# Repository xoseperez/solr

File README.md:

# Solr

The **Solr digital wrist watch** is a clock that won’t work without a battery but it will neither work without sun. Even more: the vintage display is really cool but it’s hard to read outdoors. A complete nonsense.

Check my **blog post** to know more about it: [Solr: digital wrist watch](http://tinkerman.cat/solr-digital-wrist-watch/)

## Hardware

I strongly recommend to find some provider that can assembly at least the HMC5883L, it's a really hard to chip to solder manually. The rest of the components are quite easy to do.

### BOM as exported from Eagle

|Part|Value|Package|Buy|
|---|---|---|---|
|BATT||CR2032-SMD|.|
|C1|100nf|C0805|.|
|C2|4.7uf|AVX-A|.|
|C3|220nf|C0805|.|
|C4|100nf|C0805|.|
|CHECK||BTN_CK_KSS|[Aliexpress](http://s.click.aliexpress.com/e/MrBaM7q)|
|IC1|ATMEGA328P-AU-TQFP32|TQFP32-0.8-7X7MM|[Aliexpress](http://s.click.aliexpress.com/e/Y3FMzZV)|
|IC2|HMC5883L|PLCC16-0.5-3X3MM|[Aliexpress](http://s.click.aliexpress.com/e/bIAm2zB) / [Ebay](https://rover.ebay.com/rover/1/711-53200-19255-0/1?icep_id=114&ipn=icep&toolid=20004&campid=5338044841&mpre=http%3A%2F%2Fwww.ebay.com%2Fitm%2F1x-NEW-HONEYWELL-HMC5883L-HMC-5883L-LCC16-LCC-16-IC-CHIPS-%2F321121197770)|
|LED1|HP QDSP-6064||[Ebay](https://rover.ebay.com/rover/1/1185-53479-19255-0/1?icep_id=114&ipn=icep&toolid=20004&campid=5338044841&mpre=http%3A%2F%2Fwww.ebay.es%2Fitm%2FRetro-4-digit-BUBBLE-VINTAGE-rare-red-LED-Display-QDSP6064-NOS-%2F152160249337)|
|R1|82R|R0805|.|
|R2|82R|R0805|.|
|R3|82R|R0805|.|
|R4|82R|R0805|.|
|R5|2.2K|R0805|.|
|R6|2.2K|R0805|.|
|R7|4.7K|R0805|.|

## Firmware

Check the blog post above to connect an AVR programmer to the board.

The project is ready to be build using [PlatformIO](http://www.platformio.org).
Please refer to their web page for instructions on how to install the builder.
Once installed:

```bash
> cd code
> pio run -e dev
> avrdude -v -p atmega328p -C avrdude.conf -c usbasp -Pusb -U flash:w:.pioenvs/dev/firmware.hex:i

```

Library dependencies are automatically managed via PlatformIO Library Manager.

Using PlatformIO to flash the board will probably result in an error since, by default, PlatformIO forces the -D flag on the compiler that skips the erasing process prior to flash the new project, then the verification will likely fail because out-of-boundaries memory positions will contain garbage data. That's why I'm compiling the code with PlatfomIO and flashing it directly using avrdude.

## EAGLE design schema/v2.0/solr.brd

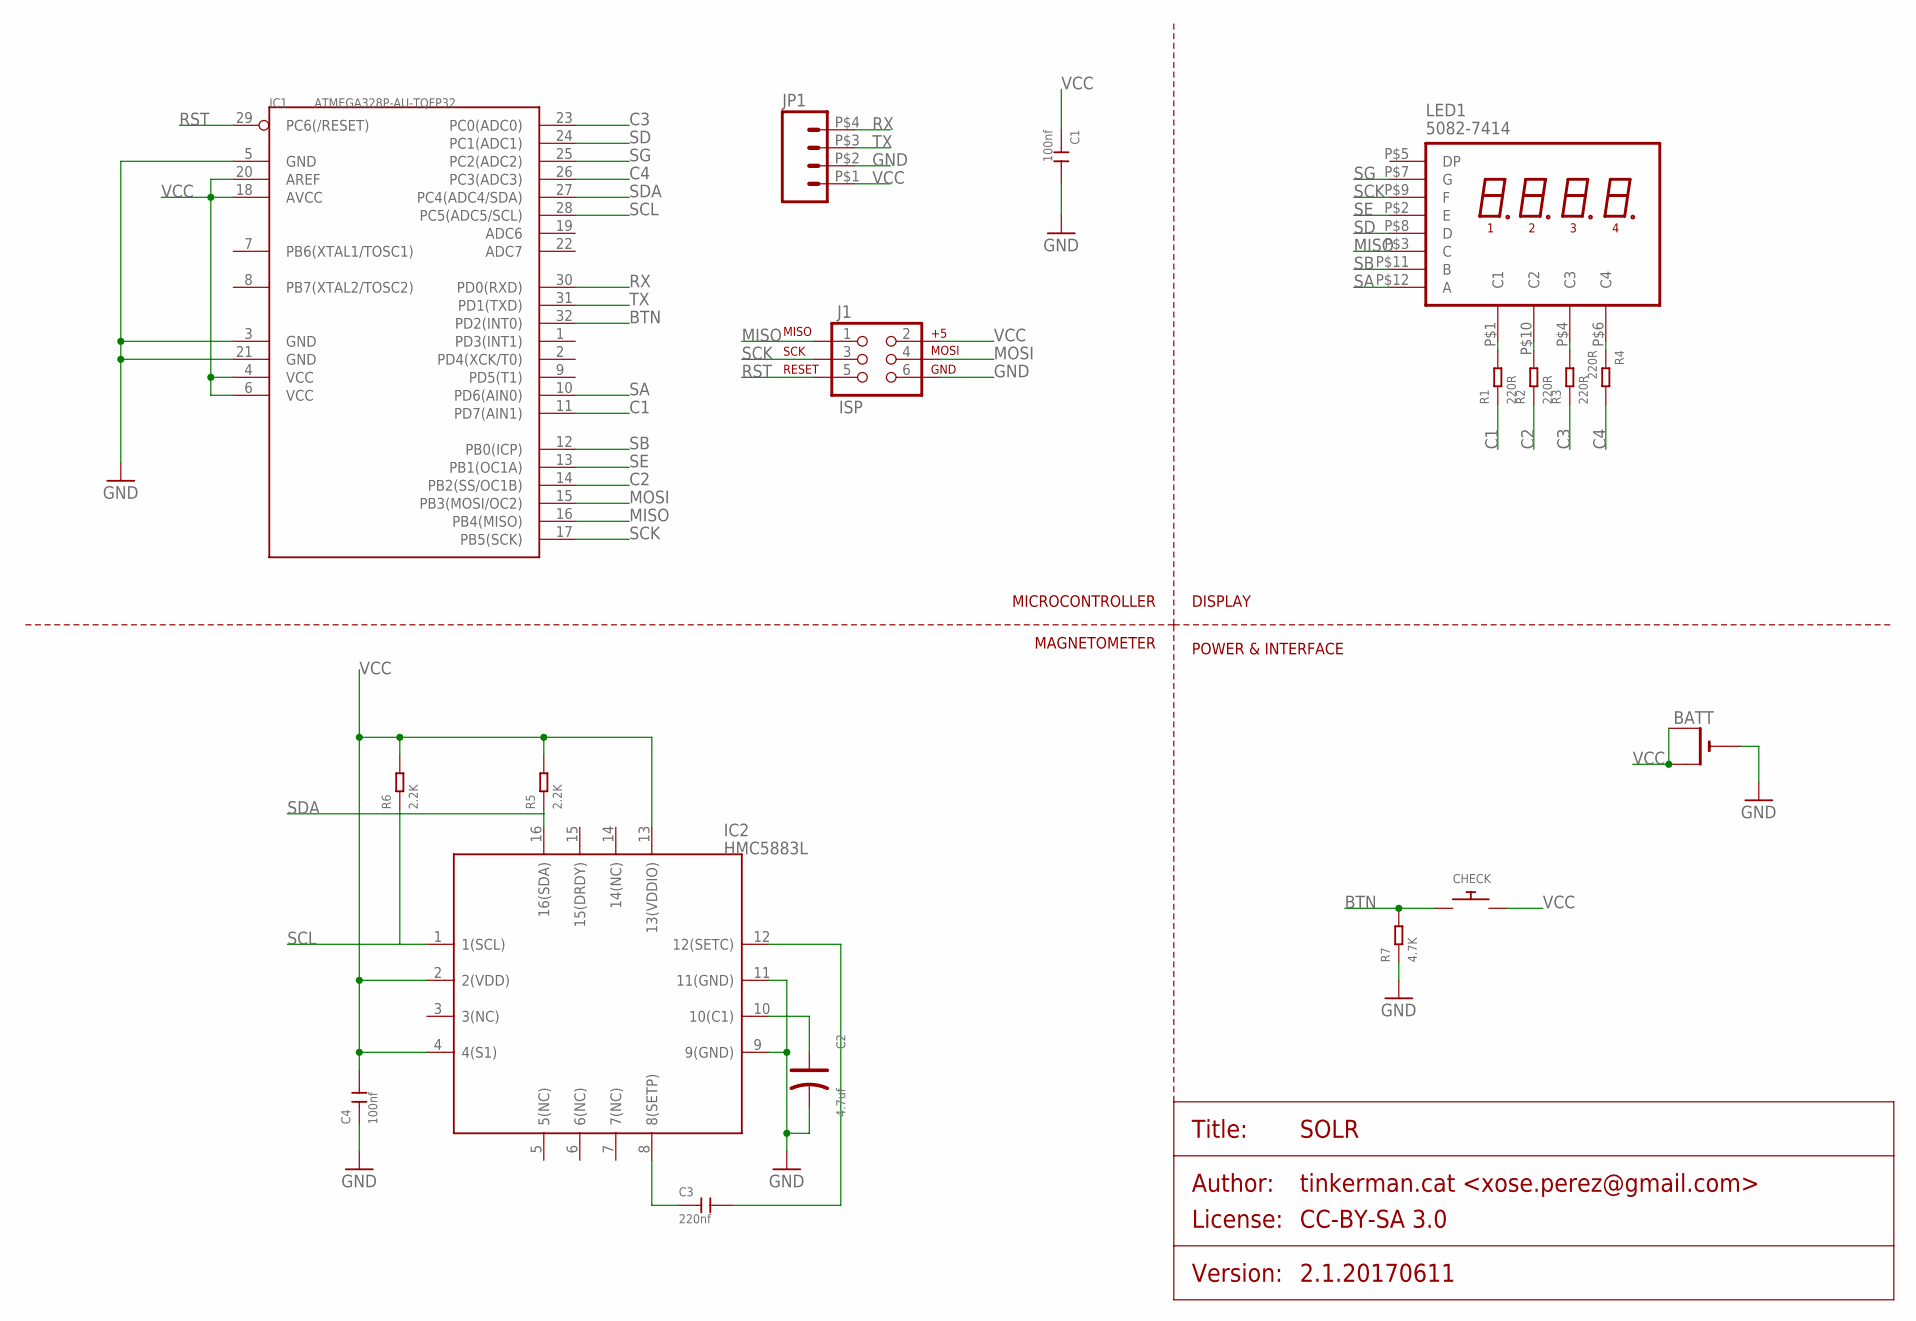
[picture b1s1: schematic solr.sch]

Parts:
BATT: CR2032SMT; CR2032-SMD
C1, C4: 100nf; C0805
C2: 4.7uf; AVX-A
C3: 220nf; C0805
CHECK: SWITCH_PUSHBUTTONC&K_KSS; BTN_CK_KSS
IC1: ATMEGA328P-AU-TQFP32; TQFP32-0.8-7X7MM
IC2: HMC5883L; PLCC16-0.5-3X3MM
J1: ISP; 2X3EDGE
JP1: M04SMD_ROUND_PADS; 1X04_SMD_ROUND_PADS
LED1: 5082-7414
R1, R2, R3, R4: 220R; R0805
R5, R6: 2.2K; R0805
R7: 4.7K; R0805

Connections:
BTN: CHECK.P$1, IC1.32 (PD2(INT0)), R7.2
C1: IC1.11 (PD7(AIN1)), R1.1
C2: IC1.14 (PB2(SS/OC1B)), R2.1
C3: IC1.23 (PC0(ADC0)), R3.1
C4: IC1.26 (PC3(ADC3)), R4.2
GND: BATT.-, C1.2, C2.-, C4.1, IC1.3 (GND), IC1.5 (GND), IC1.21 (GND), IC2.9 (9(GND)), IC2.11 (11(GND)), J1.6, JP1.P$2 (2), R7.1
MISO: IC1.16 (PB4(MISO)), J1.1, LED1.P$3 (C)
MOSI: IC1.15 (PB3(MOSI/OC2)), J1.4
unnamed: LED1.P$1 (C1), R1.2
unnamed: C3.1, IC2.8 (8(SETP))
unnamed: LED1.P$10 (C2), R2.2
unnamed: LED1.P$4 (C3), R3.2
unnamed: LED1.P$6 (C4), R4.1
unnamed: C3.2, IC2.12 (12(SETC))
unnamed: C2.+, IC2.10 (10(C1))
RST: IC1.29 (PC6(/RESET)), J1.5
RX: IC1.30 (PD0(RXD)), JP1.P$4 (4)
SA: IC1.10 (PD6(AIN0)), LED1.P$12 (A)
SB: IC1.12 (PB0(ICP)), LED1.P$11 (B)
SCK: IC1.17 (PB5(SCK)), J1.3, LED1.P$9 (F)
SCL: IC1.28 (PC5(ADC5/SCL)), IC2.1 (1(SCL)), R6.1
SD: IC1.24 (PC1(ADC1)), LED1.P$8 (D)
SDA: IC1.27 (PC4(ADC4/SDA)), IC2.16 (16(SDA)), R5.1
SE: IC1.13 (PB1(OC1A)), LED1.P$2 (E)
SG: IC1.25 (PC2(ADC2)), LED1.P$7 (G)
TX: IC1.31 (PD1(TXD)), JP1.P$3 (3)
VCC: BATT.+$1 (+), BATT.+$2 (+1), C1.1, C4.2, CHECK.P$2, IC1.4 (VCC), IC1.6 (VCC), IC1.18 (AVCC), IC1.20 (AREF), IC2.2 (2(VDD)), IC2.4 (4(S1)), IC2.13 (13(VDDIO)), J1.2, JP1.P$1 (1), R5.2, R6.2

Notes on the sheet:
MICROCONTROLLER
DISPLAY
POWER & INTERFACE
MAGNETOMETER

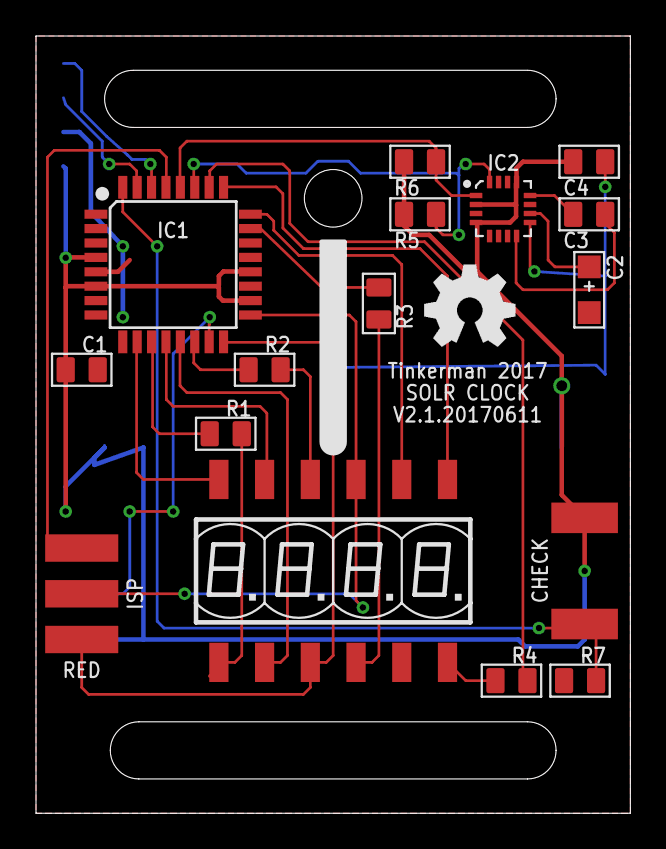
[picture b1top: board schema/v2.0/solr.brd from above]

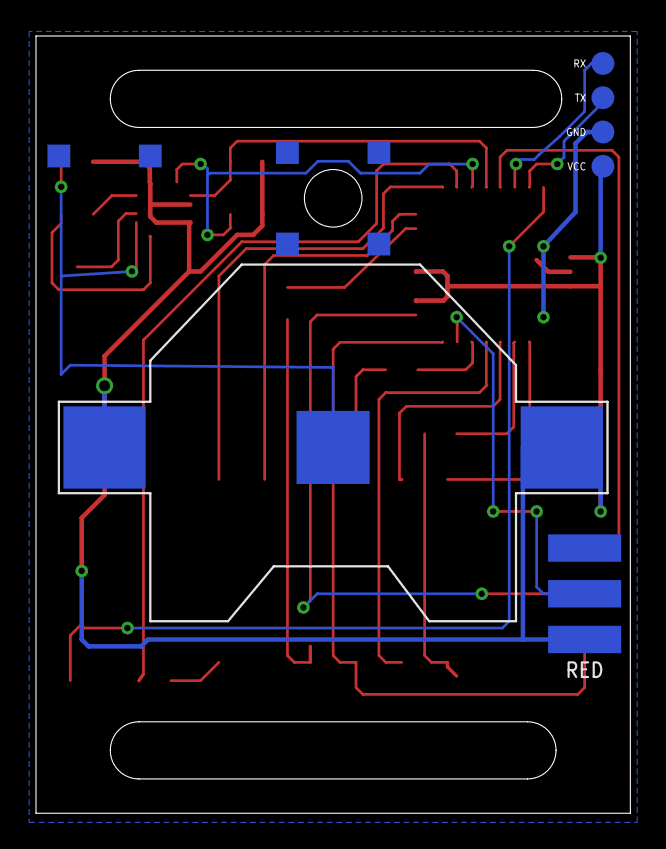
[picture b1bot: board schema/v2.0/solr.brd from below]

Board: 2 copper layers, 33.0 x 43.2 mm, 20 parts (4 on the bottom side), 27 nets.

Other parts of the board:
U$1: M3_WELDING_NUTFLAT; M3_WELDING_NUT_FLAT
U$2: M3_WELDING_NUTSTAND; M3_WELDING_NUT_STAND

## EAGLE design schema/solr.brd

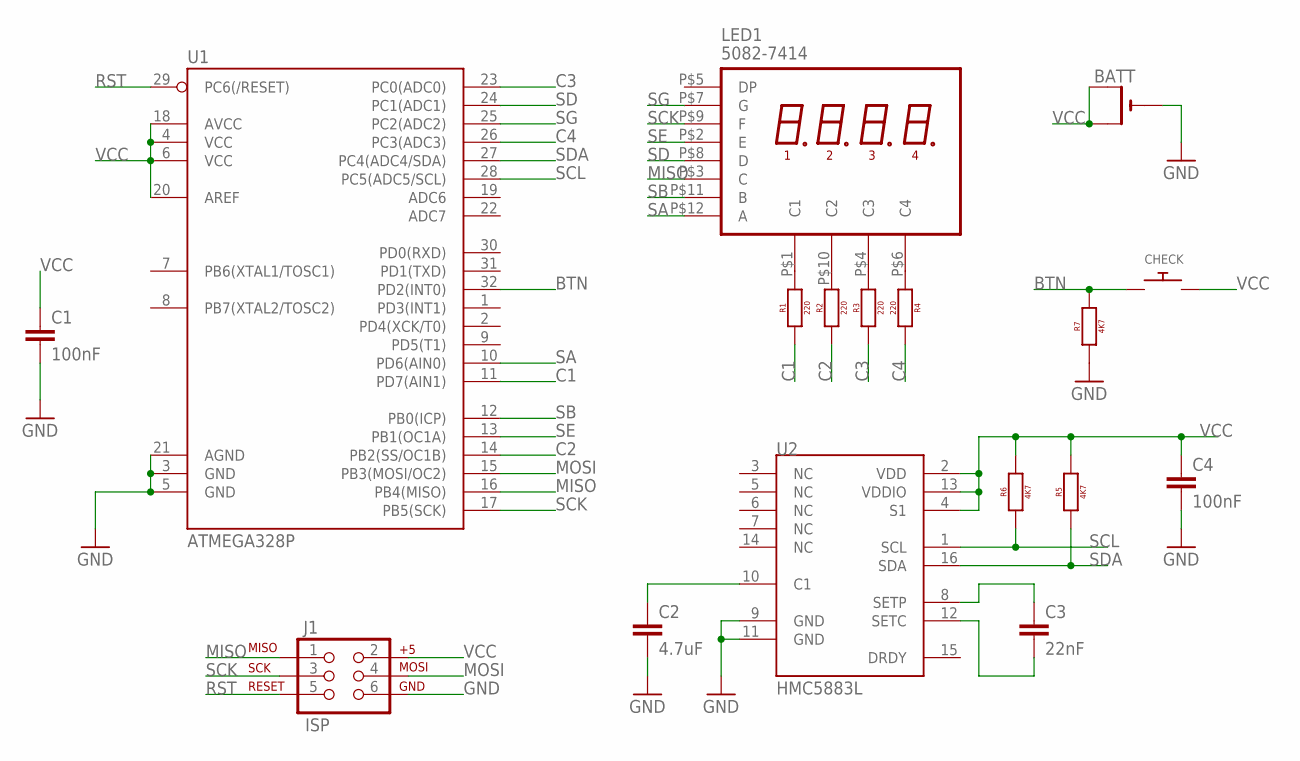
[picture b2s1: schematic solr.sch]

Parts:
BATT: CR2032SMT; CR2032-SMD
C1, C4: 100nF; 0805
C2: 4.7uF; 0805
C3: 22nF; 0805
CHECK: SWITCH_PUSHBUTTONC&K_KSS; BTN_CK_KSS
J1: ISP; 2X3EDGE
LED1: 5082-7414
R1, R2, R3, R4: 220; 0805
R5, R6, R7: 4K7; 0805
U1: ATMEGA328P; TQFP32-08
U2: HMC5883L; 16LPCC

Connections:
BTN: CHECK.P$1, R7.2, U1.32 (PD2(INT0))
C1: R1.1, U1.11 (PD7(AIN1))
C2: R2.1, U1.14 (PB2(SS/OC1B))
C3: R3.1, U1.23 (PC0(ADC0))
C4: R4.2, U1.26 (PC3(ADC3))
GND: BATT.-, C1.2, C2.2, C4.2, J1.6, R7.1, U1.3 (GND), U1.5 (GND), U1.21 (AGND), U2.9 (GND), U2.11 (GND); also elsewhere on the board
MISO: J1.1, LED1.P$3 (C), U1.16 (PB4(MISO))
MOSI: J1.4, U1.15 (PB3(MOSI/OC2))
unnamed: LED1.P$1 (C1), R1.2
unnamed: C3.1, U2.8 (SETP)
unnamed: LED1.P$10 (C2), R2.2
unnamed: LED1.P$4 (C3), R3.2
unnamed: LED1.P$6 (C4), R4.1
unnamed: C3.2, U2.12 (SETC)
unnamed: C2.1, U2.10 (C1)
RST: J1.5, U1.29 (PC6(/RESET))
RX: U1.30 (PD0(RXD)); also elsewhere on the board
SA: LED1.P$12 (A), U1.10 (PD6(AIN0))
SB: LED1.P$11 (B), U1.12 (PB0(ICP))
SCK: J1.3, LED1.P$9 (F), U1.17 (PB5(SCK))
SCL: R6.1, U1.28 (PC5(ADC5/SCL)), U2.1 (SCL)
SD: LED1.P$8 (D), U1.24 (PC1(ADC1))
SDA: R5.1, U1.27 (PC4(ADC4/SDA)), U2.16 (SDA)
SE: LED1.P$2 (E), U1.13 (PB1(OC1A))
SG: LED1.P$7 (G), U1.25 (PC2(ADC2))
TX: U1.31 (PD1(TXD)); also elsewhere on the board
VCC: BATT.+$1 (+), BATT.+$2 (+1), C1.1, C4.1, CHECK.P$2, J1.2, R5.2, R6.2, U1.4 (VCC), U1.6 (VCC), U1.18 (AVCC), U1.20 (AREF), U2.2 (VDD), U2.4 (S1), U2.13 (VDDIO); also elsewhere on the board

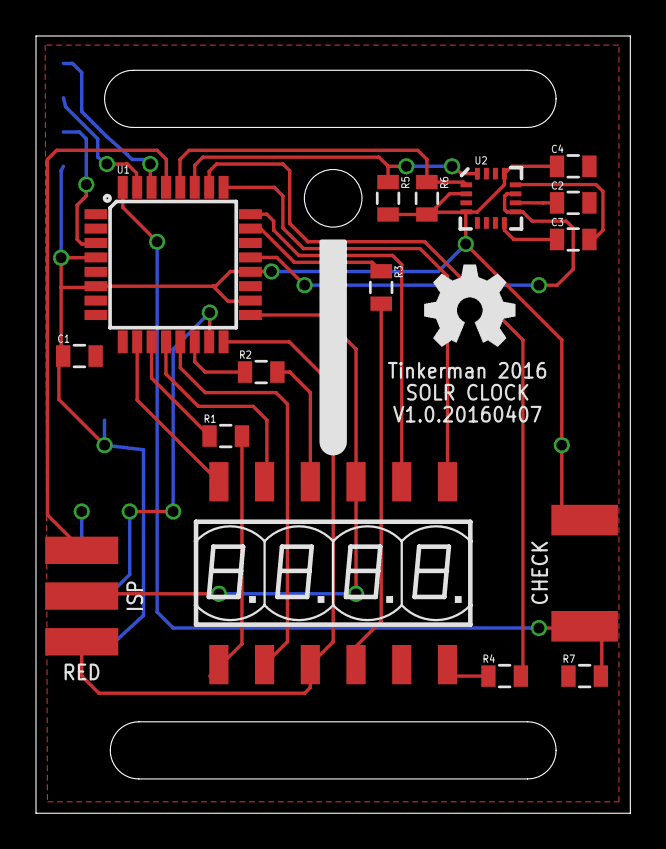
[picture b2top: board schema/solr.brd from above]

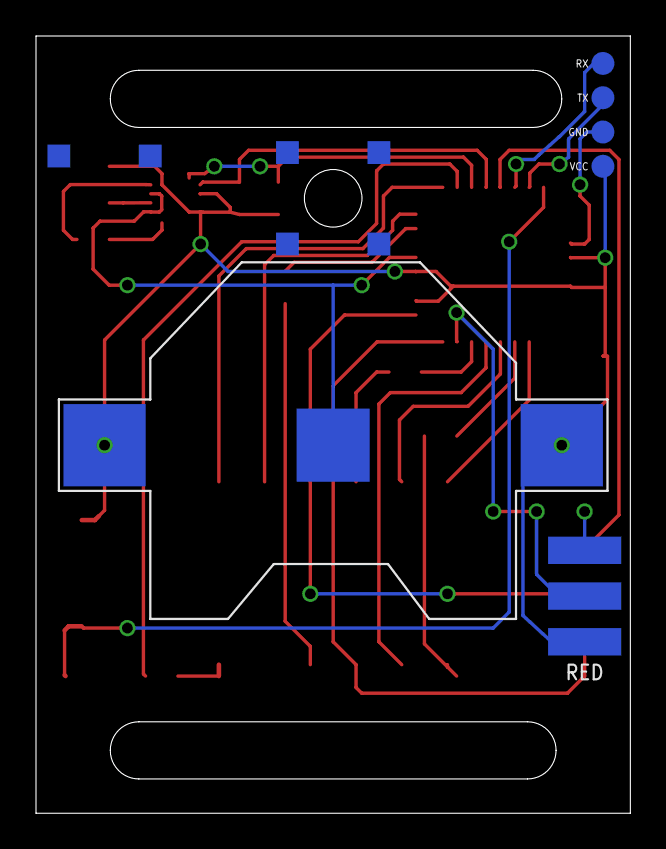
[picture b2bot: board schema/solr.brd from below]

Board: 2 copper layers, 33.0 x 43.2 mm, 20 parts (4 on the bottom side), 27 nets.

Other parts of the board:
JP1: 1X04_SMD_ROUND_PADS
U$1: M3_WELDING_NUTFLAT; M3_WELDING_NUT_FLAT
U$2: M3_WELDING_NUTSTAND; M3_WELDING_NUT_STAND

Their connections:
GND: JP1.P$2; also elsewhere on the board
RX: JP1.P$4; also elsewhere on the board
TX: JP1.P$3; also elsewhere on the board
VCC: JP1.P$1; also elsewhere on the board

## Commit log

2016-04-20 Using helscream HMC5883L calibration code with Rowberg's lilbrary, platformio environments configuration
2016-04-20 First version of the PCB sent to fab
2017-06-17 Version bump

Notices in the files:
schema/v2.0/solr.sch:
PROJECT_LICENSE: CC-BY-SA 3.0
parts and their libraries:
SparkFun-Aesthetics: Licensing: CC v3.0 Share-Alike You are welcome to use this library for commercial purposes.
